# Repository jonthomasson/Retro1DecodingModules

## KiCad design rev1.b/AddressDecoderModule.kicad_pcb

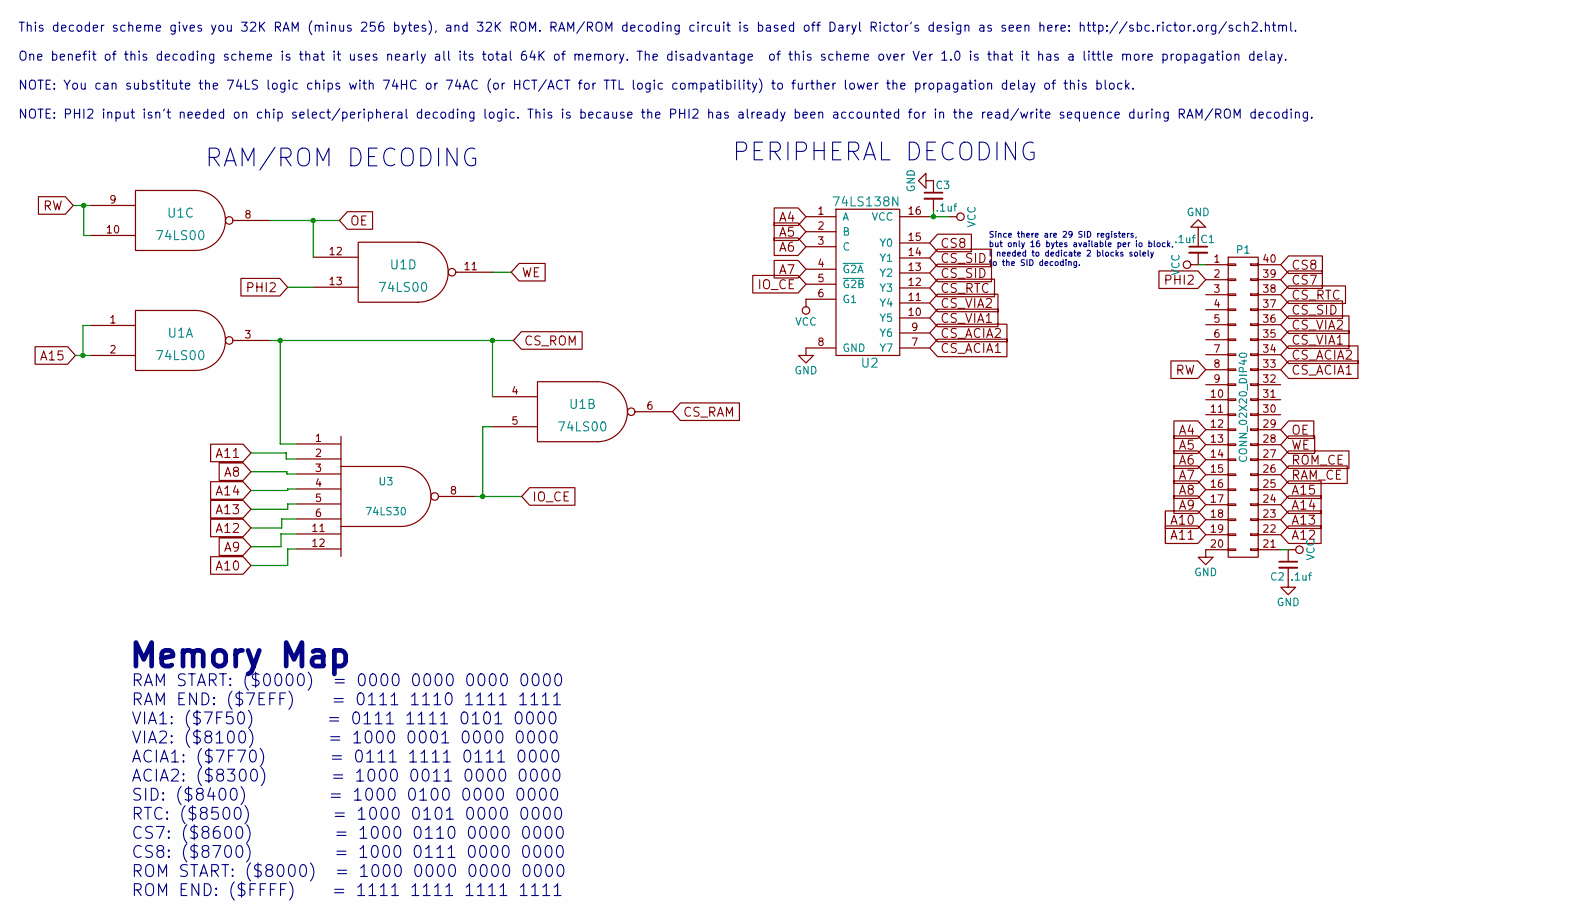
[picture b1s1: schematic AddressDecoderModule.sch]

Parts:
C1, C2, C3: .1uf; C_0805
P1: CONN_02X20_DIP40; decoder_footprint
U1: 74LS00; SOIC-14_3.9x8.7mm_Pitch1.27mm
U2: 74LS138N; SOIC-16_3.9x9.9mm_Pitch1.27mm
U3: 74LS30; SOIC-14_3.9x8.7mm_Pitch1.27mm

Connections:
A4: P1.12 (P23), U2.1 (A)
A5: P1.13 (P25), U2.2 (B)
A6: P1.14 (P27), U2.3 (C)
A7: P1.15 (P29), U2.4 (~G2A)
A8: P1.16 (P31), U3.3
A9: P1.17 (P33), U3.11
A10: P1.18 (P35), U3.12
A11: P1.19 (P37), U3.2
A12: P1.22 (P38), U3.6
A13: P1.23 (P36), U3.5
A14: P1.24 (P34), U3.4
A15: P1.25 (P32), U1.1, U1.2
CS7: P1.39 (P4)
CS8: P1.40 (P2), U2.15 (Y0)
CS_ACIA1: P1.33 (P16), U2.7 (Y7)
CS_ACIA2: P1.34 (P14), U2.9 (Y6)
CS_RAM: U1.6
CS_ROM: U1.3, U1.4, U3.1
CS_RTC: P1.38 (P6), U2.12 (Y3)
CS_SID: P1.37 (P8), U2.13 (Y2), U2.14 (Y1)
CS_VIA1: P1.35 (P12), U2.10 (Y5)
CS_VIA2: P1.36 (P10), U2.11 (Y4)
GND: C1.1, C2.2, C3.1, P1.20 (P39), U1.7 (GND), U2.8 (GND), U3.7 (GND)
IO_CE: U1.5, U2.5 (~G2B), U3.8
OE: P1.29 (P24), U1.8, U1.12
PHI2: P1.2 (P3), U1.13
RAM_CE: P1.26 (P30)
ROM_CE: P1.27 (P28)
RW: P1.8 (P15), U1.9, U1.10
VCC: C1.2, C2.1, C3.2, P1.1, P1.21 (P40), U1.14 (VCC), U2.6 (G1), U2.16 (VCC), U3.14 (VCC)
WE: P1.28 (P26), U1.11

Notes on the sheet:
RAM/ROM DECODING
PERIPHERAL DECODING
Memory Map
RAM START: ($0000) = 0000 0000 0000 0000 RAM END: ($7EFF) = 0111 1110 1111 1111 VIA1: ($7F50) = 0111 1111 0101 0000 VIA2: ($8100) = 1000 0001 0000 0000 ACIA1: ($7F70) = 0111 1111 0111 0000 ACIA2: ($8300) = 1000 0011 0000 0000 SID: ($8400) = 1000 0100 0000 0000 RTC: ($8500) = 1000 0101 0000 0000 CS7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
This decoder scheme gives you 32K RAM (minus 256 bytes), and 32K ROM. RAM/ROM decoding circuit is based off Daryl Rictor's design as seen here: http://sbc.rictor.org/sch2.html. One benefit of this decoding scheme is that it uses nearly all its total 64K of memory. The disadvantage of this scheme ov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
Since there are 29 SID registers, but only 16 bytes available per io block, I needed to dedicate 2 blocks solely to the SID decoding.

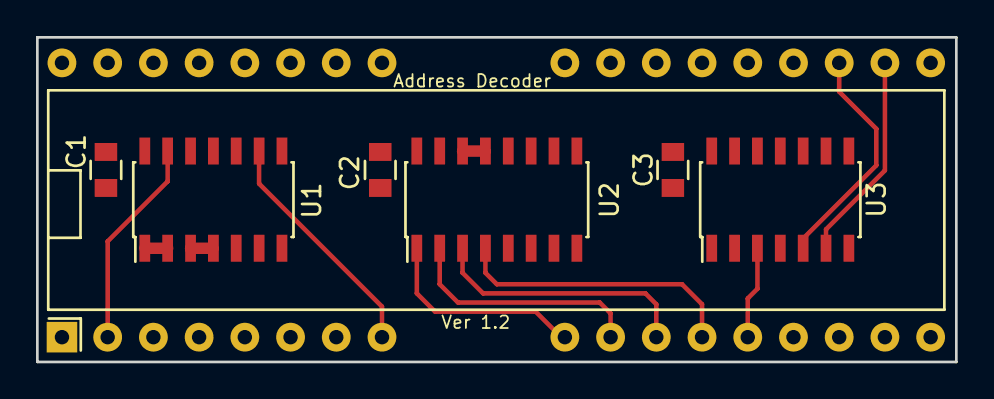
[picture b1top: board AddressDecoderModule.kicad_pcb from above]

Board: 4 copper layers, 51.1 x 18.0 mm, 7 parts (0 on the bottom side), 27 nets.

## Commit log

2017-04-17 :neckbeard: Added .gitattributes & .gitignore files
